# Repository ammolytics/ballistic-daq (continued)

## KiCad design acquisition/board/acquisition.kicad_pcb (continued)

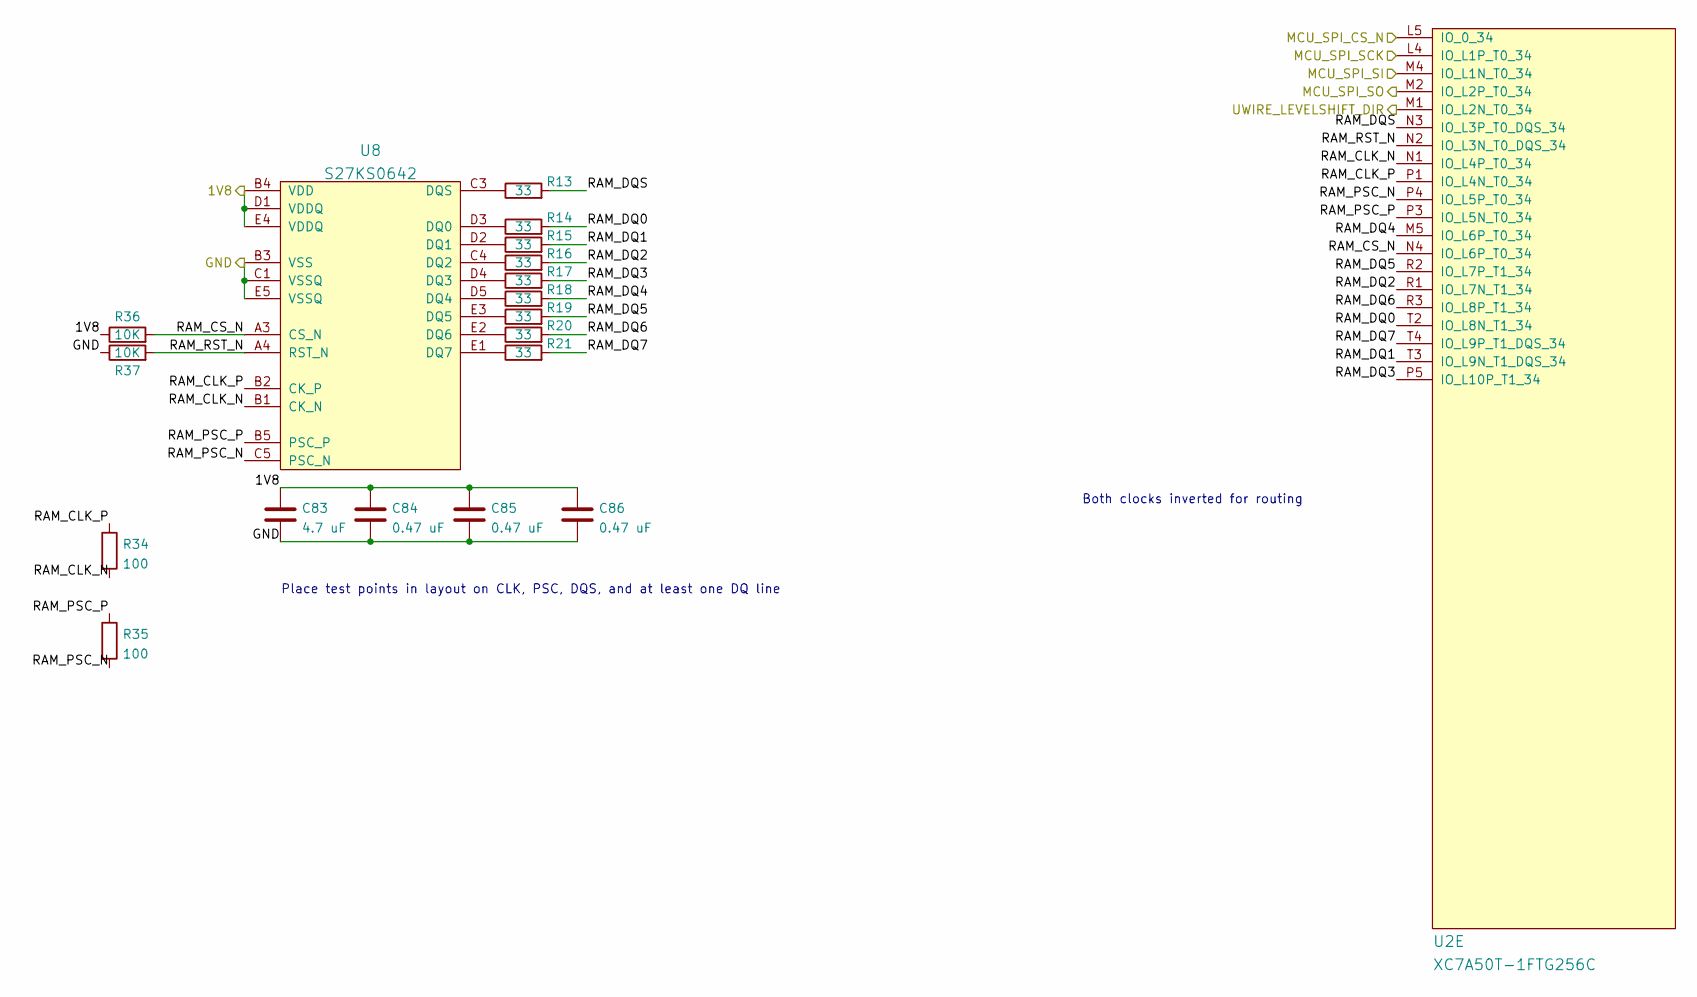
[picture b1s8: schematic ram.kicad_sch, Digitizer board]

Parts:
C83: 4.7 uF; EIA_0603_CAP_NOSILK
C84, C85, C86: 0.47 uF; EIA_0402_CAP_NOSILK
R13, R14, R15, R16, R17, R18, R19, R20, R21: 33; EIA_0402_RES_NOSILK
R34, R35: 100; EIA_0402_RES_NOSILK
R36, R37: 10K; EIA_0402_RES_NOSILK
U2: XC7A50T-1FTG256C; BGA_256_17x17_FULLARRAY_1MM_0.4MM_FTG256
U8: S27KS0642; BGA_24_6x8_DEPOP1_1MM

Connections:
/D1V8: C83.1, C84.1, C85.1, C86.1, R36.1, U8.B4 (VDD), U8.D1 (VDDQ), U8.E4 (VDDQ); also elsewhere on the board
/GND: C83.2, C84.2, C85.2, C86.2, R37.1, U8.B3 (VSS), U8.C1 (VSSQ), U8.E5 (VSSQ); also elsewhere on the board
/MCU_SPI_CS_N: U2.L5 (IO_0_34); also elsewhere on the board
/MCU_SPI_SCK: U2.L4 (IO_L1P_T0_34); also elsewhere on the board
/MCU_SPI_SI: U2.M4 (IO_L1N_T0_34); also elsewhere on the board
/MCU_SPI_SO: U2.M2 (IO_L2P_T0_34); also elsewhere on the board
/RAM/RAM_CLK_N: R34.2, U2.N1 (IO_L4P_T0_34), U8.B1 (CK_N)
/RAM/RAM_CLK_P: R34.1, U2.P1 (IO_L4N_T0_34), U8.B2 (CK_P)
/RAM/RAM_CS_N: R36.2, U2.N4 (IO_L6P_T0_34), U8.A3 (CS_N)
/RAM/RAM_DQ0: R14.2, U2.T2 (IO_L8N_T1_34)
/RAM/RAM_DQ1: R15.2, U2.T3 (IO_L9N_T1_DQS_34)
/RAM/RAM_DQ2: R16.2, U2.R1 (IO_L7N_T1_34)
/RAM/RAM_DQ3: R17.2, U2.P5 (IO_L10P_T1_34)
/RAM/RAM_DQ4: R18.2, U2.M5 (IO_L6P_T0_34)
/RAM/RAM_DQ5: R19.2, U2.R2 (IO_L7P_T1_34)
/RAM/RAM_DQ6: R20.2, U2.R3 (IO_L8P_T1_34)
/RAM/RAM_DQ7: R21.2, U2.T4 (IO_L9P_T1_DQS_34)
/RAM/RAM_DQS: R13.2, U2.N3 (IO_L3P_T0_DQS_34)
/RAM/RAM_PSC_N: R35.2, U2.P4 (IO_L5P_T0_34), U8.C5 (PSC_N)
/RAM/RAM_PSC_P: R35.1, U2.P3 (IO_L5N_T0_34), U8.B5 (PSC_P)
/RAM/RAM_RST_N: R37.2, U2.N2 (IO_L3N_T0_DQS_34), U8.A4 (RST_N)
/UWIRE_LEVELSHIFT_DIR: U2.M1 (IO_L2N_T0_34); also elsewhere on the board
unnamed: R13.1, U8.C3 (DQS)
unnamed: R14.1, U8.D3 (DQ0)
unnamed: R15.1, U8.D2 (DQ1)
unnamed: R16.1, U8.C4 (DQ2)
unnamed: R17.1, U8.D4 (DQ3)
unnamed: R18.1, U8.D5 (DQ4)
unnamed: R19.1, U8.E3 (DQ5)
unnamed: R20.1, U8.E2 (DQ6)
unnamed: R21.1, U8.E1 (DQ7)

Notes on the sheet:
Place test points in layout on CLK, PSC, DQS, and at least one DQ line
Both clocks inverted for routing

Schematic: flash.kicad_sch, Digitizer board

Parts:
C87, C89: 4.7 uF; EIA_0603_CAP_NOSILK
C88, C90: 0.47 uF; EIA_0402_CAP_NOSILK
R4, R5, R6, R7: 33; EIA_0402_RES_NOSILK
R80: 10K; EIA_0402_RES_NOSILK
R96: 4.7K; EIA_0402_RES_NOSILK
U9: S25FL128SAGBHIA10; BGA_24_6x8_DEPOP1_1MM

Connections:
/3V3: C87.1, C88.1, U9.B4 (VDD); also elsewhere on the board
/ADCs/FLASH_DQ0: R4.2; also elsewhere on the board
/ADCs/FLASH_DQ1: R5.2; also elsewhere on the board
/ADCs/FLASH_DQ2: R6.2; also elsewhere on the board
/ADCs/FLASH_DQ3: R7.2; also elsewhere on the board
/D1V8: C89.1, C90.1, R80.1, R96.2, U9.E4 (VIO); also elsewhere on the board
/FPGA support/FLASH_SCK: U9.B2 (SCK); also elsewhere on the board
/GND: C87.2, C88.2, C89.2, C90.2, U9.B3 (VSS); also elsewhere on the board
/QSPI flash/FLASH_CS_N: R96.1, U9.C2 (CS_N); also elsewhere on the board
unnamed: R4.1, U9.D3 (MOSI/DQ0)
unnamed: R5.1, U9.D2 (MISO/DQ1)
unnamed: R6.1, U9.C4 (WP_N/DQ2)
unnamed: R7.1, U9.D4 (RESET_N/DQ3)
unnamed: R80.2, U9.A4 (RESET_N)

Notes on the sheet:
128 Mbits 133 MHz with 3.3V IO Max of 66 MHz with 1.8V IO EHPLC 5x5 ball with RESET# and VIO Uniform 256 kB sectors

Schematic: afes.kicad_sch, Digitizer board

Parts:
D4, D5, D6, D7, D8, D9, D10, D11, D12, D13, D14, D15, D16, D17, D18, D19: TPD1E05U06QDPYRQ1; DFN_2_1x0.6_TI_DPY
J2, J3, J4, J5, J6, J7, J8, J9, J10, J11, J12, J13, J14, J15, J16, J17: MMCX; CONN_MMCX_J_P_H_ST_EM1

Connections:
/ADCs/IN0_N: D12.1 (K), J3.1 (In); also elsewhere on the board
/ADCs/IN0_P: D4.1 (K), J2.1 (In); also elsewhere on the board
/ADCs/IN1_N: D13.1 (K), J5.1 (In); also elsewhere on the board
/ADCs/IN1_P: D5.1 (K), J4.1 (In); also elsewhere on the board
/ADCs/IN2_N: D14.1 (K), J7.1 (In); also elsewhere on the board
/ADCs/IN2_P: D6.1 (K), J6.1 (In); also elsewhere on the board
/ADCs/IN3_N: D15.1 (K), J9.1 (In); also elsewhere on the board
/ADCs/IN3_P: D7.1 (K), J8.1 (In); also elsewhere on the board
/ADCs/IN4_N: D16.1 (K), J11.1 (In); also elsewhere on the board
/ADCs/IN4_P: D8.1 (K), J10.1 (In); also elsewhere on the board
/ADCs/IN5_N: D17.1 (K), J13.1 (In); also elsewhere on the board
/ADCs/IN5_P: D9.1 (K), J12.1 (In); also elsewhere on the board
/ADCs/IN6_N: D18.1 (K), J15.1 (In); also elsewhere on the board
/ADCs/IN6_P: D10.1 (K), J14.1 (In); also elsewhere on the board
/ADCs/IN7_N: D19.1 (K), J17.1 (In); also elsewhere on the board
/ADCs/IN7_P: D11.1 (K), J16.1 (In); also elsewhere on the board
/GND: D4.2 (A), D5.2 (A), D6.2 (A), D7.2 (A), D8.2 (A), D9.2 (A), D10.2 (A), D11.2 (A), D12.2 (A), D13.2 (A), D14.2 (A), D15.2 (A), D16.2 (A), D17.2 (A), D18.2 (A), D19.2 (A), J2.2 (Ext), J3.2 (Ext), J4.2 (Ext), J5.2 (Ext), J6.2 (Ext), J7.2 (Ext), J8.2 (Ext), J9.2 (Ext), J10.2 (Ext), J11.2 (Ext), J12.2 (Ext), J13.2 (Ext), J14.2 (Ext), J15.2 (Ext), J16.2 (Ext), J17.2 (Ext); also elsewhere on the board

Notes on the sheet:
100 ohm differential analog inputs +/- 1V differential range External differential amplifier required on sensor module board (suggest ADA4938) Common mode voltage is 900 mV
ESD protection for analog inputs

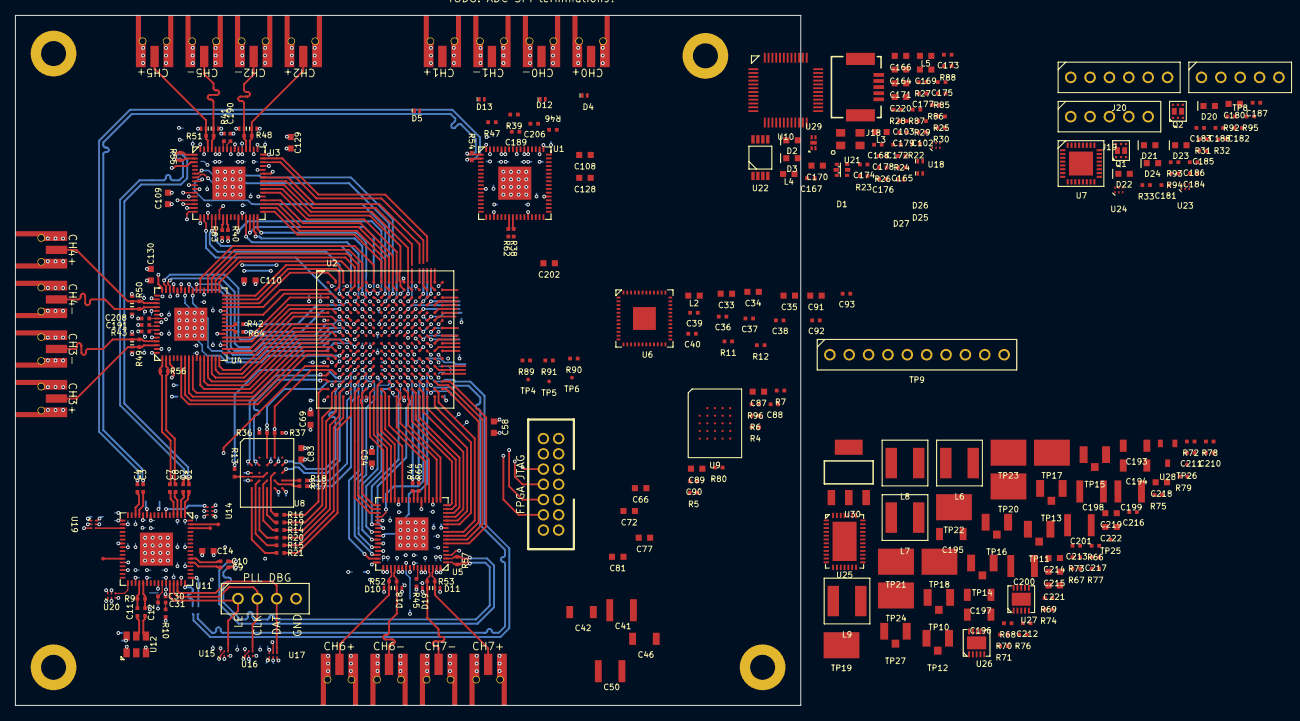
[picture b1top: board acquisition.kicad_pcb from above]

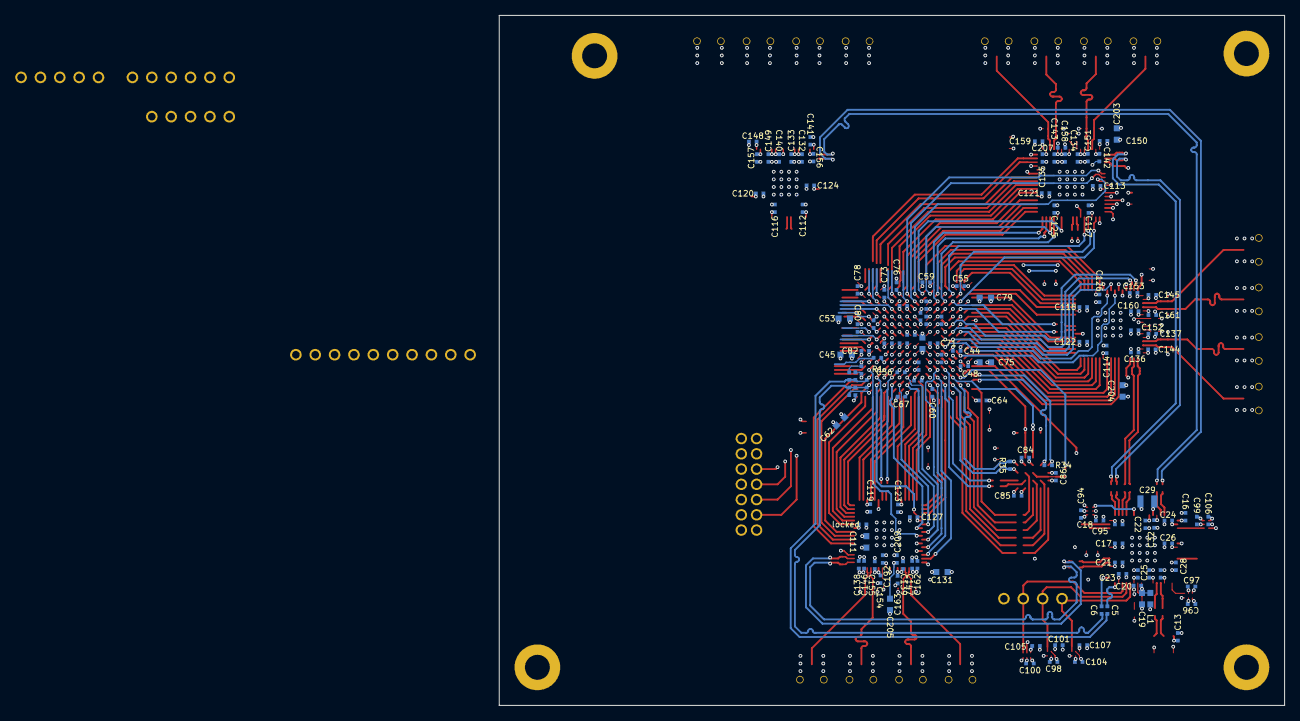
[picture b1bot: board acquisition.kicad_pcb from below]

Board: 6 copper layers, 103.0 x 90.5 mm, 432 parts (132 on the bottom side), 367 nets.

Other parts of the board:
locked: 0.47 uF; EIA_0402_CAP_NOSILK

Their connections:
/D1V8: locked.1; also elsewhere on the board
/GND: locked.2; also elsewhere on the board

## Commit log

2022-04-16 Initial design notes
2022-06-21 Initial schematic skeleton
2022-06-23 Continued initial design
2022-07-05 Updated schematic with a lot of level shifting and support stuff, power decoupling, etc. Almost done except power supply and protection diodes
2022-07-06 Lots of progress on power supply design, added a bunch of test points, etc
2022-07-08 More power supply work, added PLL loop filter, soft start, began assigning footprints
2022-07-17 Completed schematic after design review, ready for layout
2023-01-30 Finished footprint assignment
2023-01-30 Initial layout floorplanning
2023-01-31 Finished initial routing of RAM, hooked up almost all of first ADC
2023-01-31 Continued layout of bottom ADC, routed FPGA JTAG
2023-02-01 Began layout of clocking subsystem
2023-02-02 Continued layout of clocking subsystem, second ADC, and BGA fanout
2023-02-03 Hooked up power and analog connections to third ADC, no data bus yet
2023-02-04 Routed most of third ADC data bus
2023-02-04 Fully routed ADC #3
2023-02-04 Initial placement and power/clock routing for fourth ADC
